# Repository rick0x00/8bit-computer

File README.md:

# 8bit-computer

This project intends to develop and distribute following the principles of the [Open Source Initiative(OSI)](https://opensource.org/osd).

The project was based on the model presented by [Wagner Rambo](https://youtube.com/playlist?list=PLZ8dBTV2_5HTB43Mhfz-TyIATkECrp8XY) and also by the project presented by [Ben Eater](https://youtube.com/playlist?list=PLowKtXNTBypGqImE405J2565dvjafglHU), both on youtube!

## Warning
I, the project maintainer ,am a beginner in this Open Source world, Git, GitHub... So I apologize in advance for any problems.

## License
At the present time this project is completely under [Apache 2.0 license](http://www.apache.org/licenses/LICENSE-2.0). All Softwares, All Electronic Designs(Schematics), All Documentation and All 3D Design.

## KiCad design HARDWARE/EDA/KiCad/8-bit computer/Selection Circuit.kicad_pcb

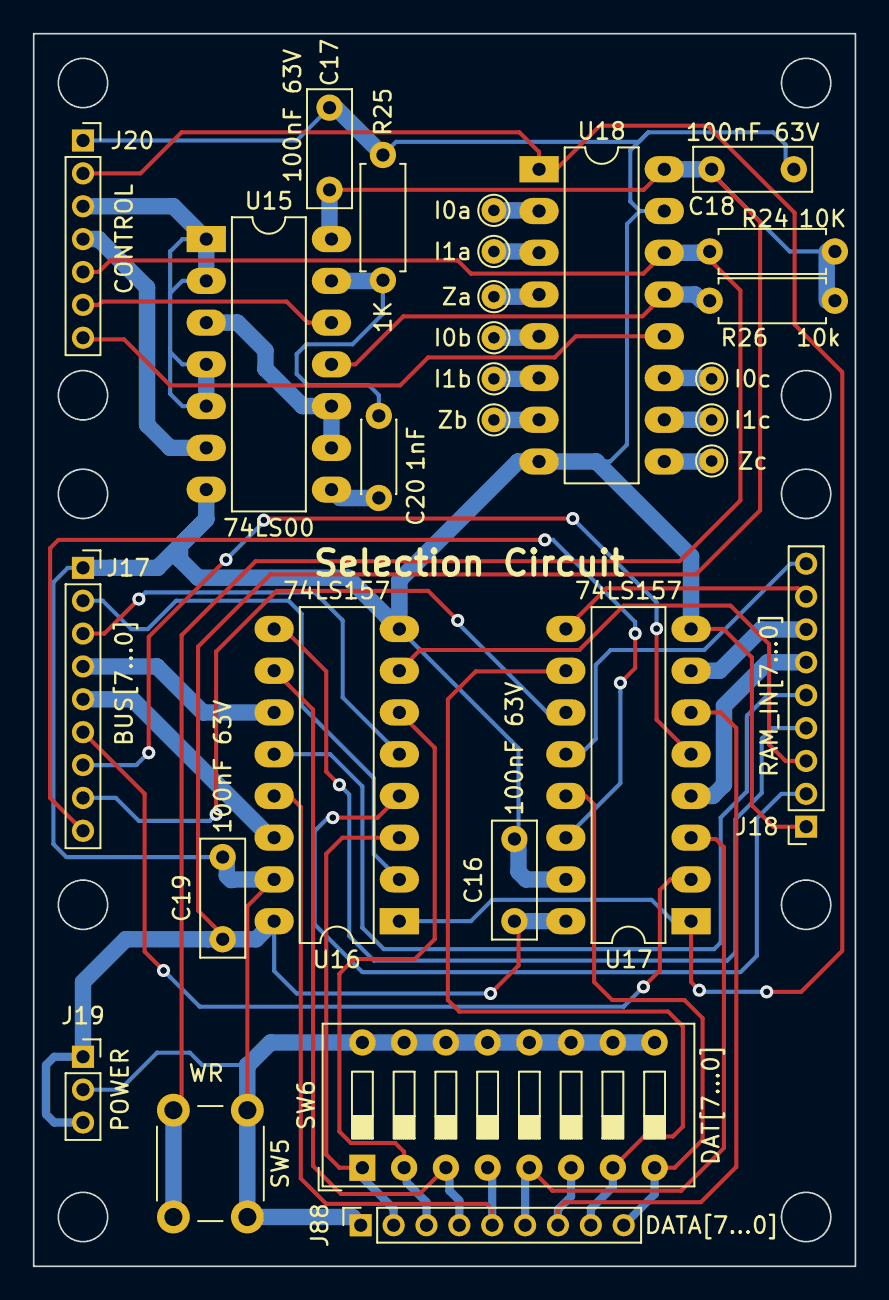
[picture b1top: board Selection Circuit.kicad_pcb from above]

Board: 2 copper layers, 50.0 x 75.0 mm, 28 parts (0 on the bottom side), 45 nets.

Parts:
C16, C17, C18, C19: 100nF 63V; C_Rect_L7.0mm_W2.5mm_P5.00mm
C20: 1nF; C_Disc_D4.3mm_W1.9mm_P5.00mm
J17: BUS[7...0]; PinSocket_1x09_P2.00mm_Vertical
J18: RAM_IN[7...0]; PinSocket_1x09_P2.00mm_Vertical
J19: POWER; PinSocket_1x03_P2.00mm_Vertical
J20: CONTROL; PinSocket_1x07_P2.00mm_Vertical
J88: DATA[7...0]; PinSocket_1x09_P2.00mm_Vertical
R24: 10K; R_Axial_DIN0207_L6.3mm_D2.5mm_P7.62mm_Horizontal
R25: 1K; R_Axial_DIN0207_L6.3mm_D2.5mm_P7.62mm_Horizontal
R26: 10k; R_Axial_DIN0207_L6.3mm_D2.5mm_P7.62mm_Horizontal
SW5: WR; SW_PUSH_6mm_H5mm
SW6: DAT[7...0]; SW_DIP_SPSTx08_Slide_9.78x22.5mm_W7.62mm_P2.54mm
TP26: I0a; TestPoint_THTPad_D1.5mm_Drill0.7mm
TP27: I1a; TestPoint_THTPad_D1.5mm_Drill0.7mm
TP28: I0b; TestPoint_THTPad_D1.5mm_Drill0.7mm
TP29: I1b; TestPoint_THTPad_D1.5mm_Drill0.7mm
TP30: I0c; TestPoint_THTPad_D1.5mm_Drill0.7mm
TP31: I1c; TestPoint_THTPad_D1.5mm_Drill0.7mm
TP32: Za; TestPoint_THTPad_D1.5mm_Drill0.7mm
TP33: Zb; TestPoint_THTPad_D1.5mm_Drill0.7mm
TP34: Zc; TestPoint_THTPad_D1.5mm_Drill0.7mm
U15: 74LS00; DIP-14_W7.62mm_LongPads
U16, U17, U18: 74LS157; DIP-16_W7.62mm_LongPads

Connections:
+5V: C16.1, C17.1, C18.1, C19.1, J19.1, J19.3, R24.1, R26.1, U15.14, U16.16, U17.16, U18.16
/dat0: J88.2, SW6.1, U16.3
/dat1: J88.3, SW6.2, U16.6
/dat2: J88.4, SW6.3, U16.10
/dat3: J88.5, SW6.4, U16.13
/dat4: J88.6, SW6.5, U17.3
/dat5: J88.7, SW6.6, U17.6
/dat6: J88.8, SW6.7, U17.10
/dat7: J88.9, SW6.8, U17.13
CLOCK: J20.3, U15.1, U15.2, U15.4, U15.5
GND: C16.2, C17.2, C18.2, C19.2, J17.1, J18.1, J19.2, J20.1, J88.1, R25.2, SW5.1, SW6.9, SW6.10, SW6.11, SW6.12, SW6.13, SW6.14, SW6.15, SW6.16, U15.7, U16.8, U16.15, U17.8, U17.15, U18.8, U18.15
unnamed: C20.1, R25.1, U15.13
unnamed: C20.2, U15.8
unnamed: R26.2, U15.11, U18.13
unnamed: TP26.1, U18.2
unnamed: TP27.1, U18.3
unnamed: TP28.1, U18.5
unnamed: TP29.1, U18.6
unnamed: TP30.1, U18.11
unnamed: TP31.1, U18.10
unnamed: TP32.1, U18.4
unnamed: TP33.1, U18.7
unnamed: TP34.1, U18.9
unnamed: U15.3, U15.9, U15.10
RAM_IN: J20.6, U15.12
WR_BUTTON: J20.5, R24.2, SW5.2, U18.14
\CLOCK: J20.4, U15.6
\Program,Run: J20.2, U16.1, U17.1, U18.1
\WE: J20.7, U18.12
bus0: J17.2, U16.2
bus1: J17.3, U16.5
bus2: J17.4, U16.11
bus3: J17.5, U16.14
bus4: J17.6, U17.2
bus5: J17.7, U17.5
bus6: J17.8, U17.11
bus7: J17.9, U17.14
ram_in0: J18.2, U16.4
ram_in1: J18.3, U16.7
ram_in2: J18.4, U16.9
ram_in3: J18.5, U16.12
ram_in4: J18.6, U17.4
ram_in5: J18.7, U17.7
ram_in6: J18.8, U17.9
ram_in7: J18.9, U17.12

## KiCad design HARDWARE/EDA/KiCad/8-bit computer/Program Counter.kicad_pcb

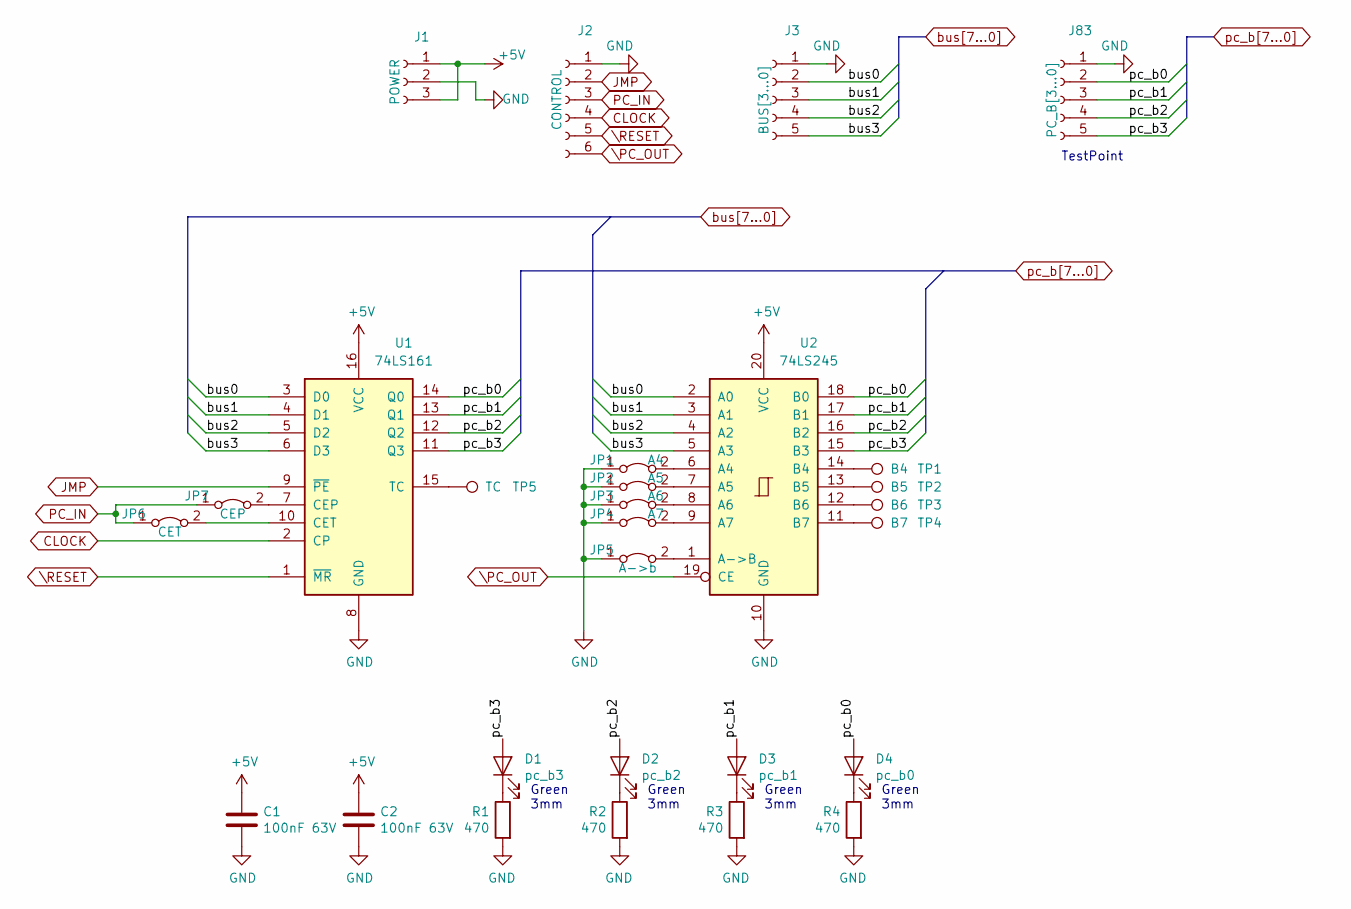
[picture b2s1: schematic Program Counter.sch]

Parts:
C1, C2: 100nF 63V; C_Rect_L7.0mm_W2.5mm_P5.00mm
D1: pc_b3; LED_D3.0mm
D2: pc_b2; LED_D3.0mm
D3: pc_b1; LED_D3.0mm
D4: pc_b0; LED_D3.0mm
J1: POWER; PinSocket_1x03_P2.00mm_Vertical
J2: CONTROL; PinSocket_1x06_P2.00mm_Vertical
J3: BUS[3...0]; PinSocket_1x05_P2.00mm_Vertical
J83: PC_B[3...0]; PinSocket_1x05_P2.00mm_Vertical
JP1: A4; TestPoint_2Pads_Pitch2.54mm_Drill0.8mm
JP2: A5; TestPoint_2Pads_Pitch2.54mm_Drill0.8mm
JP3: A6; TestPoint_2Pads_Pitch2.54mm_Drill0.8mm
JP4: A7; TestPoint_2Pads_Pitch2.54mm_Drill0.8mm
JP5: A->b; TestPoint_2Pads_Pitch2.54mm_Drill0.8mm
JP6: CET; TestPoint_2Pads_Pitch2.54mm_Drill0.8mm
JP7: CEP; TestPoint_2Pads_Pitch2.54mm_Drill0.8mm
R1, R2, R3, R4: 470; R_Axial_DIN0207_L6.3mm_D2.5mm_P7.62mm_Horizontal
TP1: B4; TestPoint_THTPad_D1.5mm_Drill0.7mm
TP2: B5; TestPoint_THTPad_D1.5mm_Drill0.7mm
TP3: B6; TestPoint_THTPad_D1.5mm_Drill0.7mm
TP4: B7; TestPoint_THTPad_D1.5mm_Drill0.7mm
TP5: TC; TestPoint_THTPad_D1.5mm_Drill0.7mm
U1: 74LS161; DIP-16_W7.62mm_LongPads
U2: 74LS245; DIP-20_W7.62mm_LongPads

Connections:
+5V: C1.1, C2.1, J1.1, J1.3, U1.16 (VCC), U2.20 (VCC)
CLOCK: J2.4, U1.2 (CP)
GND: C1.2, C2.2, J1.2, J2.1, J3.1, J83.1, JP1.1 (A), JP2.1 (A), JP3.1 (A), JP4.1 (A), JP5.1 (A), R1.2, R2.2, R3.2, R4.2, U1.8 (GND), U2.10 (GND)
JMP: J2.2, U1.9 (~PE)
unnamed: D1.1 (K), R1.1
unnamed: D2.1 (K), R2.1
unnamed: D3.1 (K), R3.1
unnamed: D4.1 (K), R4.1
unnamed: JP1.2 (B), U2.6 (A4)
unnamed: JP2.2 (B), U2.7 (A5)
unnamed: JP3.2 (B), U2.8 (A6)
unnamed: JP4.2 (B), U2.9 (A7)
unnamed: JP5.2 (B), U2.1 (A->B)
unnamed: JP6.2 (B), U1.10 (CET)
unnamed: JP7.2 (B), U1.7 (CEP)
unnamed: TP1.1, U2.14 (B4)
unnamed: TP2.1, U2.13 (B5)
unnamed: TP3.1, U2.12 (B6)
unnamed: TP4.1, U2.11 (B7)
unnamed: TP5.1, U1.15 (TC)
PC_IN: J2.3, JP6.1 (A), JP7.1 (A)
\PC_OUT: J2.6, U2.19 (CE)
\RESET: J2.5, U1.1 (~MR)
bus0: J3.2, U1.3 (D0), U2.2 (A0)
bus1: J3.3, U1.4 (D1), U2.3 (A1)
bus2: J3.4, U1.5 (D2), U2.4 (A2)
bus3: J3.5, U1.6 (D3), U2.5 (A3)
pc_b0: D4.2 (A), J83.2, U1.14 (Q0), U2.18 (B0)
pc_b1: D3.2 (A), J83.3, U1.13 (Q1), U2.17 (B1)
pc_b2: D2.2 (A), J83.4, U1.12 (Q2), U2.16 (B2)
pc_b3: D1.2 (A), J83.5, U1.11 (Q3), U2.15 (B3)

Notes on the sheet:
Green 3mm
TestPoint

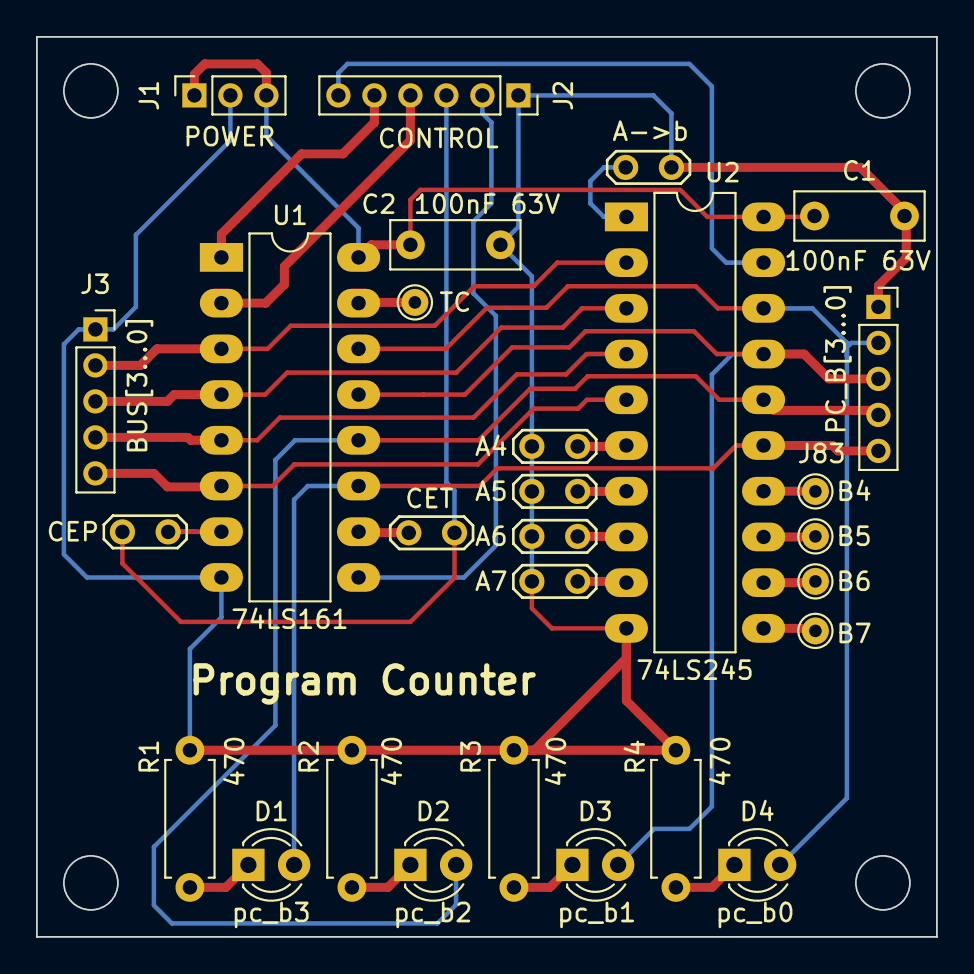
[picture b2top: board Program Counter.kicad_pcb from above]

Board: 2 copper layers, 50.0 x 50.0 mm, 28 parts (0 on the bottom side), 31 nets.

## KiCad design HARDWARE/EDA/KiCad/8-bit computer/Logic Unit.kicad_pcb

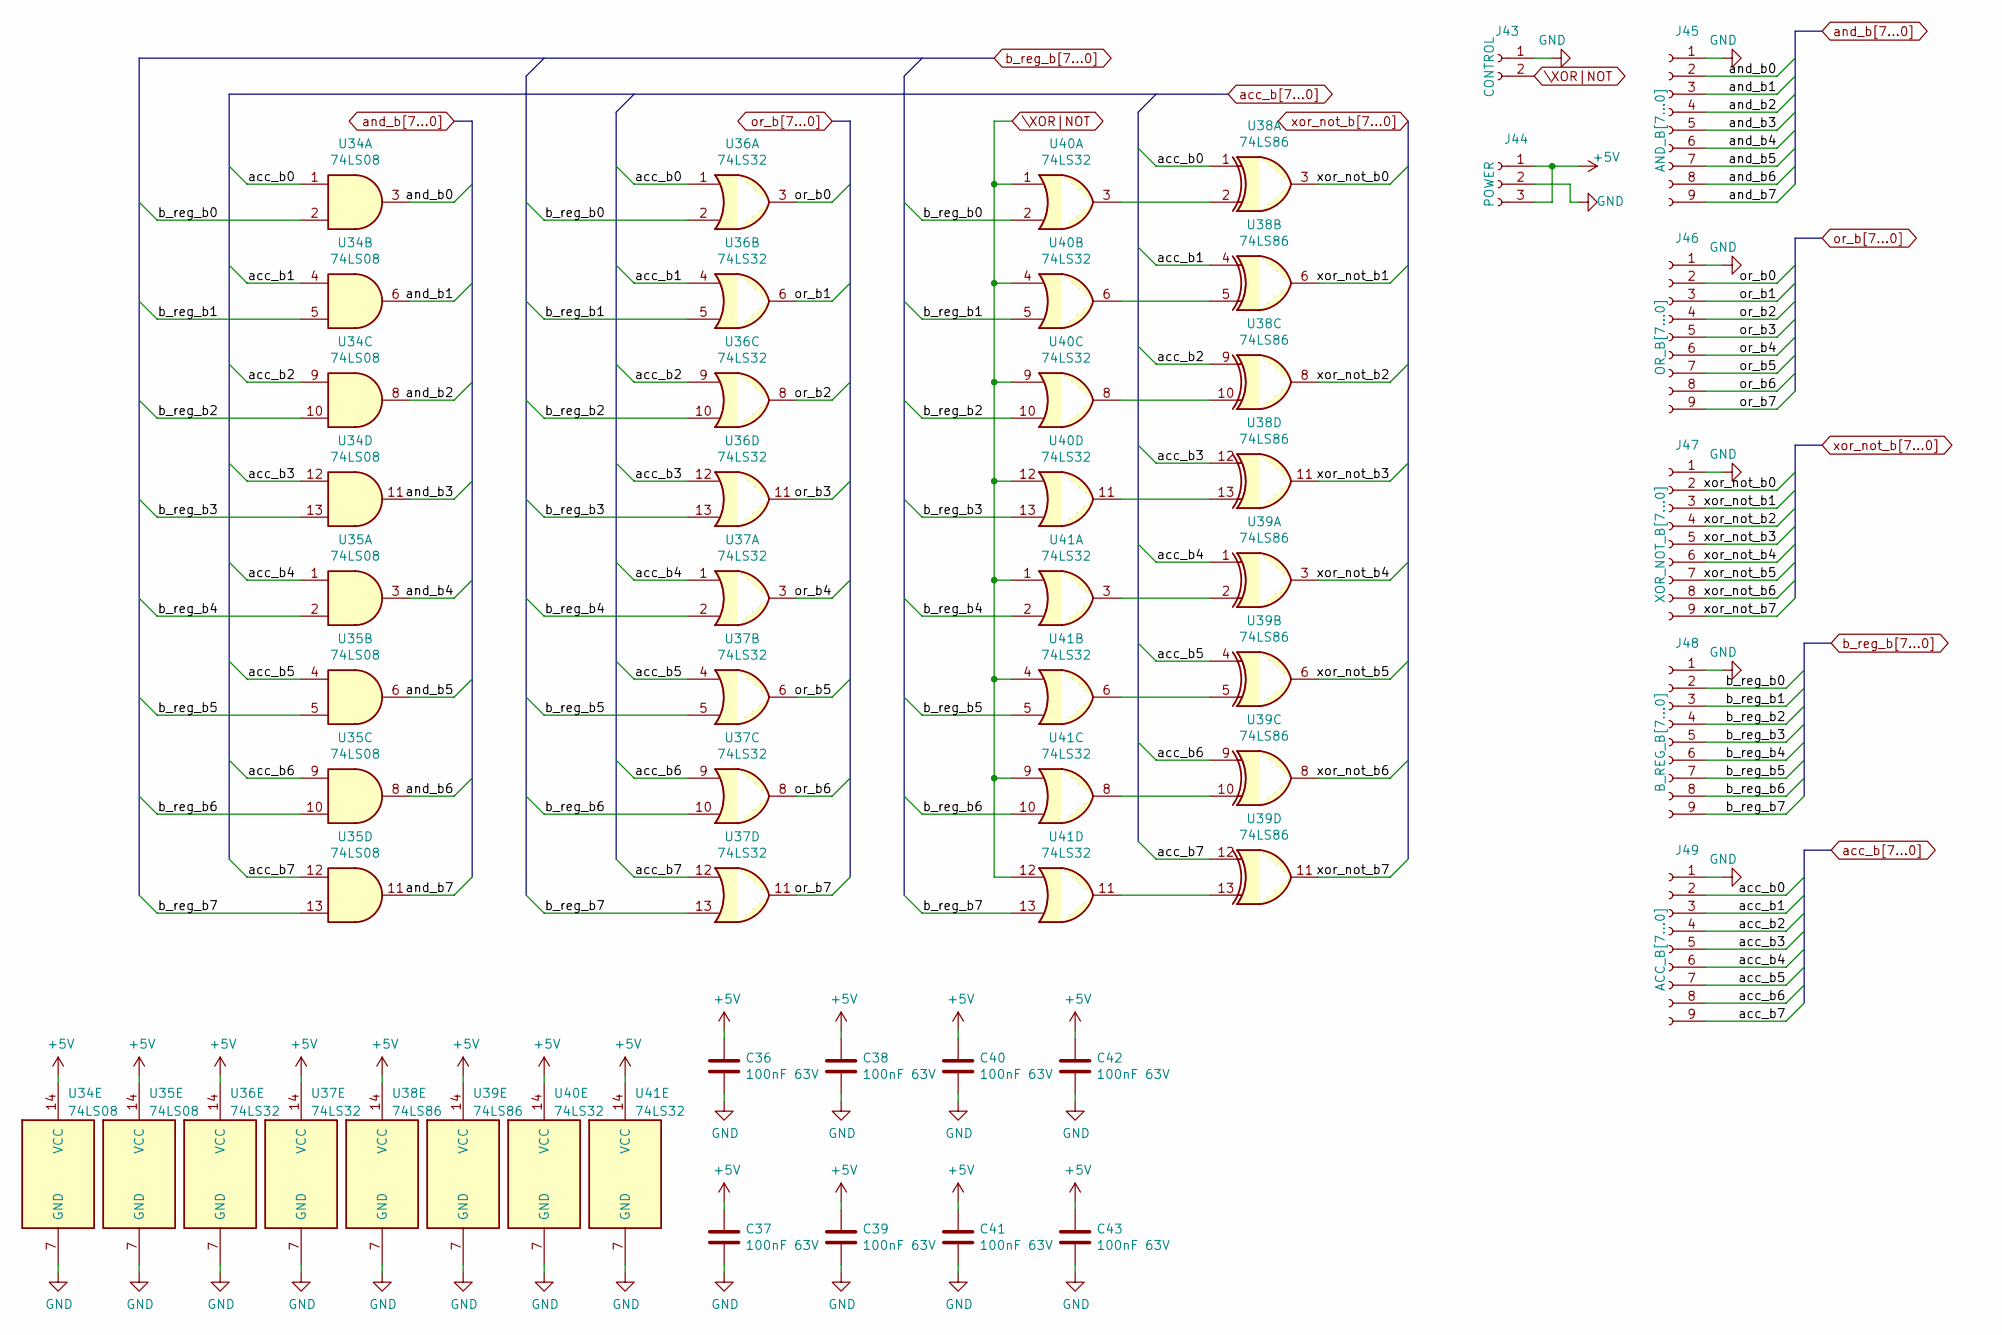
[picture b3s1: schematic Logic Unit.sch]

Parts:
C36, C37, C38, C39, C40, C41, C42, C43: 100nF 63V; C_Rect_L7.0mm_W2.5mm_P5.00mm
J43: CONTROL; PinSocket_1x02_P2.00mm_Vertical
J44: POWER; PinSocket_1x03_P2.00mm_Vertical
J45: AND_B[7...0]; PinSocket_1x09_P2.00mm_Vertical
J46: OR_B[7...0]; PinSocket_1x09_P2.00mm_Vertical
J47: XOR_NOT_B[7...0]; PinSocket_1x09_P2.00mm_Vertical
J48: B_REG_B[7...0]; PinSocket_1x09_P2.00mm_Vertical
J49: ACC_B[7...0]; PinSocket_1x09_P2.00mm_Vertical
U34, U35: 74LS08; DIP-14_W7.62mm_LongPads
U36, U37, U40, U41: 74LS32; DIP-14_W7.62mm_LongPads
U38, U39: 74LS86; DIP-14_W7.62mm_LongPads

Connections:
+5V: C36.1, C37.1, C38.1, C39.1, C40.1, C41.1, C42.1, C43.1, J44.1, J44.3, U34.14 (VCC), U35.14 (VCC), U36.14 (VCC), U37.14 (VCC), U38.14 (VCC), U39.14 (VCC), U40.14 (VCC), U41.14 (VCC)
GND: C36.2, C37.2, C38.2, C39.2, C40.2, C41.2, C42.2, C43.2, J43.1, J44.2, J45.1, J46.1, J47.1, J48.1, J49.1, U34.7 (GND), U35.7 (GND), U36.7 (GND), U37.7 (GND), U38.7 (GND), U39.7 (GND), U40.7 (GND), U41.7 (GND)
unnamed: U38.2, U40.3
unnamed: U38.5, U40.6
unnamed: U38.10, U40.8
unnamed: U38.13, U40.11
unnamed: U39.2, U41.3
unnamed: U39.5, U41.6
unnamed: U39.10, U41.8
unnamed: U39.13, U41.11
\XOR|NOT: J43.2, U40.1, U40.4, U40.9, U40.12, U41.1, U41.4, U41.9, U41.12
acc_b0: J49.2, U34.1, U36.1, U38.1
acc_b1: J49.3, U34.4, U36.4, U38.4
acc_b2: J49.4, U34.9, U36.9, U38.9
acc_b3: J49.5, U34.12, U36.12, U38.12
acc_b4: J49.6, U35.1, U37.1, U39.1
acc_b5: J49.7, U35.4, U37.4, U39.4
acc_b6: J49.8, U35.9, U37.9, U39.9
acc_b7: J49.9, U35.12, U37.12, U39.12
and_b0: J45.2, U34.3
and_b1: J45.3, U34.6
and_b2: J45.4, U34.8
and_b3: J45.5, U34.11
and_b4: J45.6, U35.3
and_b5: J45.7, U35.6
and_b6: J45.8, U35.8
and_b7: J45.9, U35.11
b_reg_b0: J48.2, U34.2, U36.2, U40.2
b_reg_b1: J48.3, U34.5, U36.5, U40.5
b_reg_b2: J48.4, U34.10, U36.10, U40.10
b_reg_b3: J48.5, U34.13, U36.13, U40.13
b_reg_b4: J48.6, U35.2, U37.2, U41.2
b_reg_b5: J48.7, U35.5, U37.5, U41.5
b_reg_b6: J48.8, U35.10, U37.10, U41.10
b_reg_b7: J48.9, U35.13, U37.13, U41.13
or_b0: J46.2, U36.3
or_b1: J46.3, U36.6
or_b2: J46.4, U36.8
or_b3: J46.5, U36.11
or_b4: J46.6, U37.3
or_b5: J46.7, U37.6
or_b6: J46.8, U37.8
or_b7: J46.9, U37.11
xor_not_b0: J47.2, U38.3
xor_not_b1: J47.3, U38.6
xor_not_b2: J47.4, U38.8
xor_not_b3: J47.5, U38.11
xor_not_b4: J47.6, U39.3
xor_not_b5: J47.7, U39.6
xor_not_b6: J47.8, U39.8
xor_not_b7: J47.9, U39.11

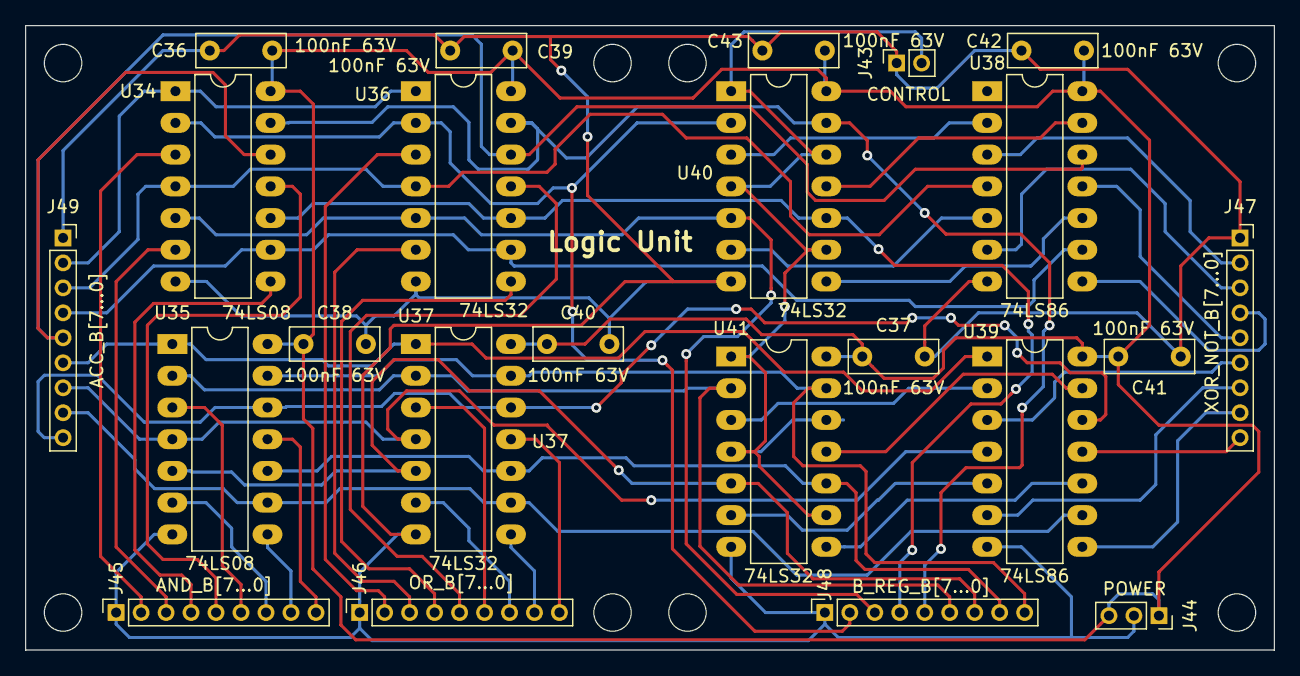
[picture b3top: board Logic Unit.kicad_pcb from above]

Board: 2 copper layers, 100.0 x 50.0 mm, 23 parts (0 on the bottom side), 51 nets.

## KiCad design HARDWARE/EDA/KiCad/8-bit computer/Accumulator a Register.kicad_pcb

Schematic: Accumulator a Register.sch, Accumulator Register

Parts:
C24, C25, C26: 100nF 63V; C_Rect_L7.0mm_W2.5mm_P5.00mm
D27: acc_b7; LED_D3.0mm
D28: acc_b6; LED_D3.0mm
D29: acc_b5; LED_D3.0mm
D30: acc_b4; LED_D3.0mm
D31: acc_b3; LED_D3.0mm
D32: acc_b2; LED_D3.0mm
D33: acc_b1; LED_D3.0mm
D34: acc_b0; LED_D3.0mm
J25: POWER; PinSocket_1x03_P2.00mm_Vertical
J26: CONTROL; PinSocket_1x05_P2.00mm_Vertical
J27: ACC_B[7...0]; PinSocket_1x09_P2.00mm_Vertical
J28: BUS[7...0]; PinSocket_1x09_P2.00mm_Vertical
JP25, JP29: Oe2; TestPoint_2Pads_Pitch2.54mm_Drill0.8mm
JP26, JP30: E2; TestPoint_2Pads_Pitch2.54mm_Drill0.8mm
JP27, JP31: Oe1; TestPoint_2Pads_Pitch2.54mm_Drill0.8mm
JP28, JP32: E1; TestPoint_2Pads_Pitch2.54mm_Drill0.8mm
JP33: A->B; TestPoint_2Pads_Pitch2.54mm_Drill0.8mm
R35, R36, R37, R38, R39, R40, R41, R42: 470; R_Axial_DIN0207_L6.3mm_D2.5mm_P7.62mm_Horizontal
U22, U23: 74LS173; DIP-16_W7.62mm_LongPads
U24: 74LS245; DIP-20_W7.62mm_LongPads

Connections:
+5V: C24.1, C25.1, C26.1, J25.1, J25.3, JP33.1 (A), U22.16, U23.16, U24.20 (VCC)
CLOCK: J26.2, U22.7, U23.7
GND: C24.2, C25.2, C26.2, J25.2, J26.1, J27.1, J28.1, JP25.1 (A), JP27.1 (A), JP29.1 (A), JP31.1 (A), R35.2, R36.2, R37.2, R38.2, R39.2, R40.2, R41.2, R42.2, U22.8, U23.8, U24.10 (GND)
unnamed: D27.1 (K), R35.1
unnamed: D28.1 (K), R36.1
unnamed: D29.1 (K), R37.1
unnamed: D30.1 (K), R38.1
unnamed: D31.1 (K), R39.1
unnamed: D32.1 (K), R40.1
unnamed: D33.1 (K), R41.1
unnamed: D34.1 (K), R42.1
unnamed: JP25.2 (B), U22.2
unnamed: JP26.2 (B), U22.10
unnamed: JP27.2 (B), U22.1
unnamed: JP28.2 (B), U22.9
unnamed: JP29.2 (B), U23.2
unnamed: JP30.2 (B), U23.10
unnamed: JP31.2 (B), U23.1
unnamed: JP32.2 (B), U23.9
unnamed: JP33.2 (B), U24.1 (A->B)
RESET: J26.3, U22.15, U23.15
\ACC_IN: J26.4, JP26.1 (A), JP28.1 (A), JP30.1 (A), JP32.1 (A)
\ACC_OUT: J26.5, U24.19 (CE)
acc_b0: D34.2 (A), J27.2, U22.3, U24.2 (A0)
acc_b1: D33.2 (A), J27.3, U22.4, U24.3 (A1)
acc_b2: D32.2 (A), J27.4, U22.5, U24.4 (A2)
acc_b3: D31.2 (A), J27.5, U22.6, U24.5 (A3)
acc_b4: D30.2 (A), J27.6, U23.3, U24.6 (A4)
acc_b5: D29.2 (A), J27.7, U23.4, U24.7 (A5)
acc_b6: D28.2 (A), J27.8, U23.5, U24.8 (A6)
acc_b7: D27.2 (A), J27.9, U23.6, U24.9 (A7)
bus0: J28.2, U22.14, U24.18 (B0)
bus1: J28.3, U22.13, U24.17 (B1)
bus2: J28.4, U22.12, U24.16 (B2)
bus3: J28.5, U22.11, U24.15 (B3)
bus4: J28.6, U23.14, U24.14 (B4)
bus5: J28.7, U23.13, U24.13 (B5)
bus6: J28.8, U23.12, U24.12 (B6)
bus7: J28.9, U23.11, U24.11 (B7)

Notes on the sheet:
Green 3mm
Red 3mm

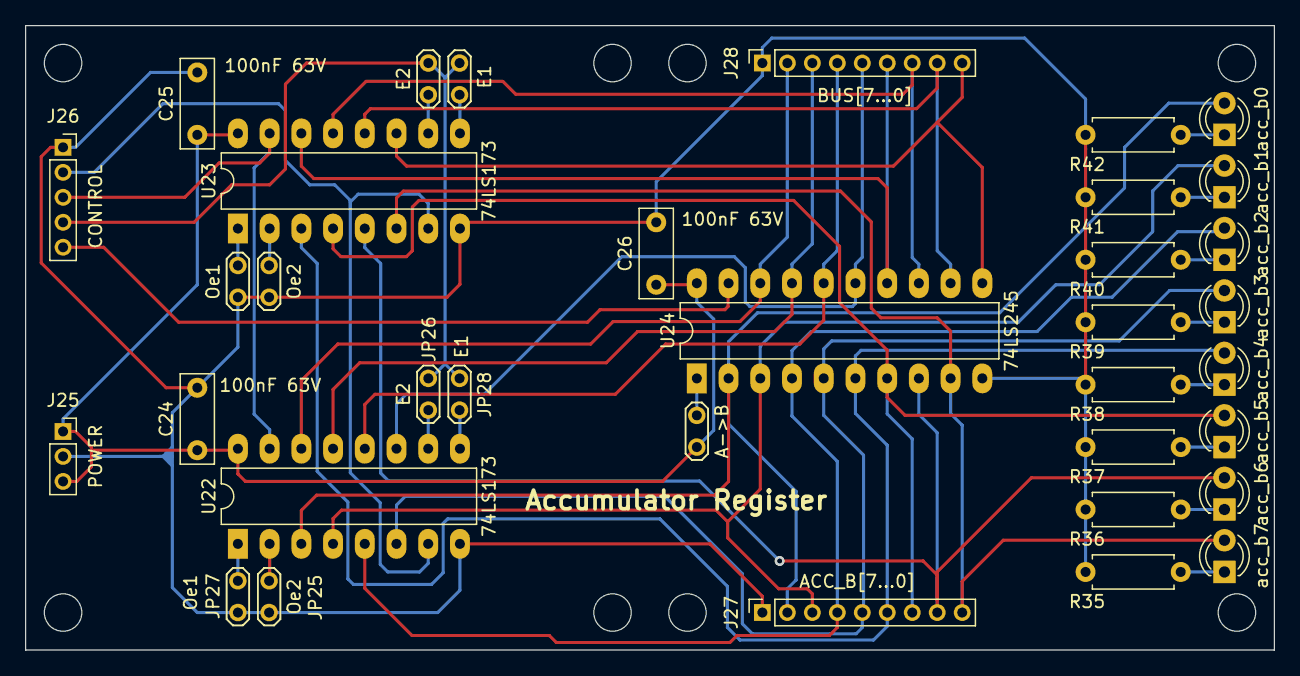
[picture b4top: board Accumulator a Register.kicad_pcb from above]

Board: 2 copper layers, 100.0 x 50.0 mm, 35 parts (0 on the bottom side), 39 nets.

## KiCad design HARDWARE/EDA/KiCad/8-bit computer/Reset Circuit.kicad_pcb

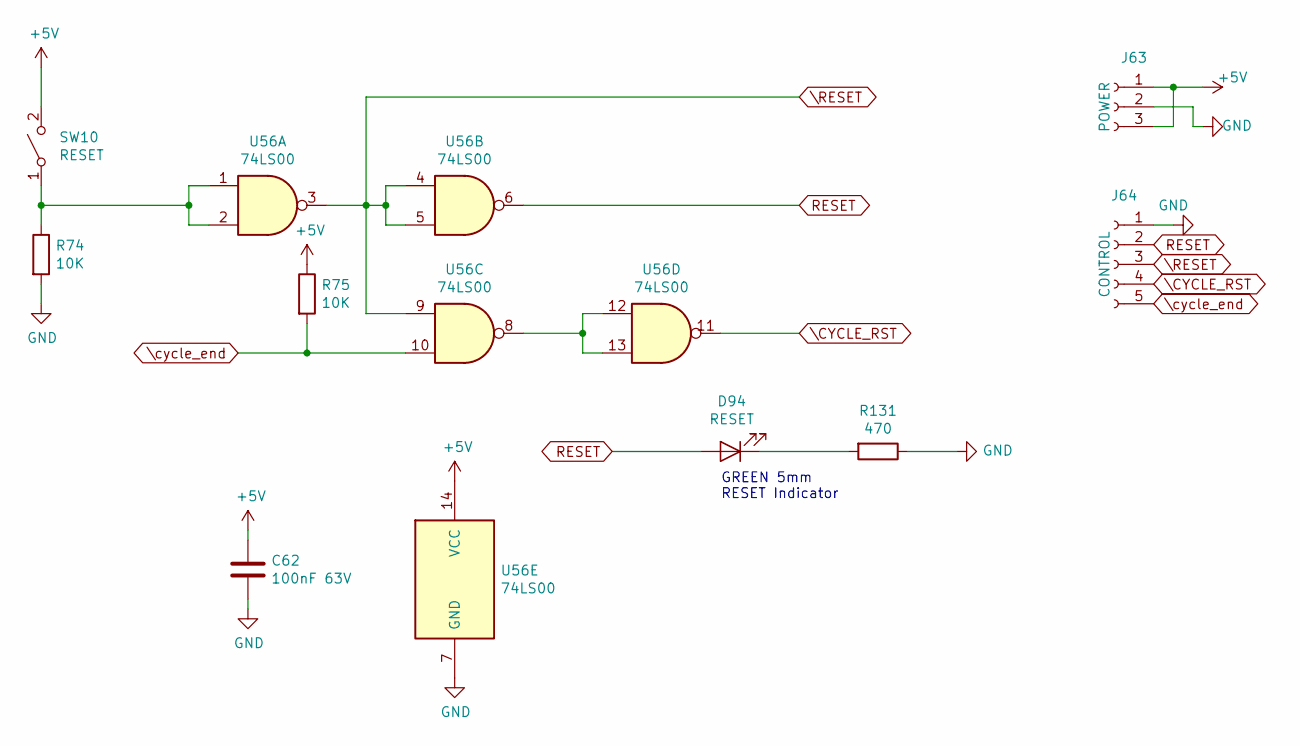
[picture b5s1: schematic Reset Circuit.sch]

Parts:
C62: 100nF 63V; C_Rect_L7.0mm_W2.5mm_P5.00mm
D94: RESET; LED_D3.0mm
J63: POWER; PinSocket_1x03_P2.00mm_Vertical
J64: CONTROL; PinSocket_1x05_P2.00mm_Vertical
R74, R75: 10K; R_Axial_DIN0207_L6.3mm_D2.5mm_P7.62mm_Horizontal
R131: 470; R_Axial_DIN0207_L6.3mm_D2.5mm_P7.62mm_Horizontal
SW10: RESET; SW_PUSH_6mm_H5mm
U56: 74LS00; DIP-14_W7.62mm_LongPads

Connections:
+5V: C62.1, J63.1, J63.3, R75.1, SW10.2 (B), U56.14 (VCC)
GND: C62.2, J63.2, J64.1, R74.2, R131.1, U56.7 (GND)
unnamed: D94.1 (K), R131.2
unnamed: R74.1, SW10.1 (A), U56.1, U56.2
unnamed: U56.8, U56.12, U56.13
RESET: D94.2 (A), J64.2, U56.6
\CYCLE_RST: J64.4, U56.11
\RESET: J64.3, U56.3, U56.4, U56.5, U56.9
\cycle_end: J64.5, R75.2, U56.10

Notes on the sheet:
GREEN 5mm RESET Indicator

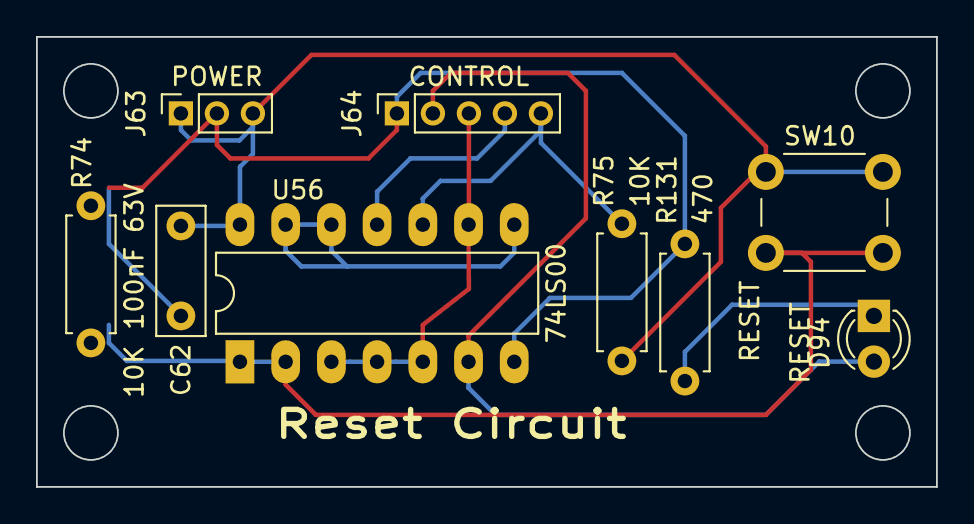
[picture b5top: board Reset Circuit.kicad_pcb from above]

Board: 2 copper layers, 50.0 x 25.0 mm, 9 parts (0 on the bottom side), 9 nets.

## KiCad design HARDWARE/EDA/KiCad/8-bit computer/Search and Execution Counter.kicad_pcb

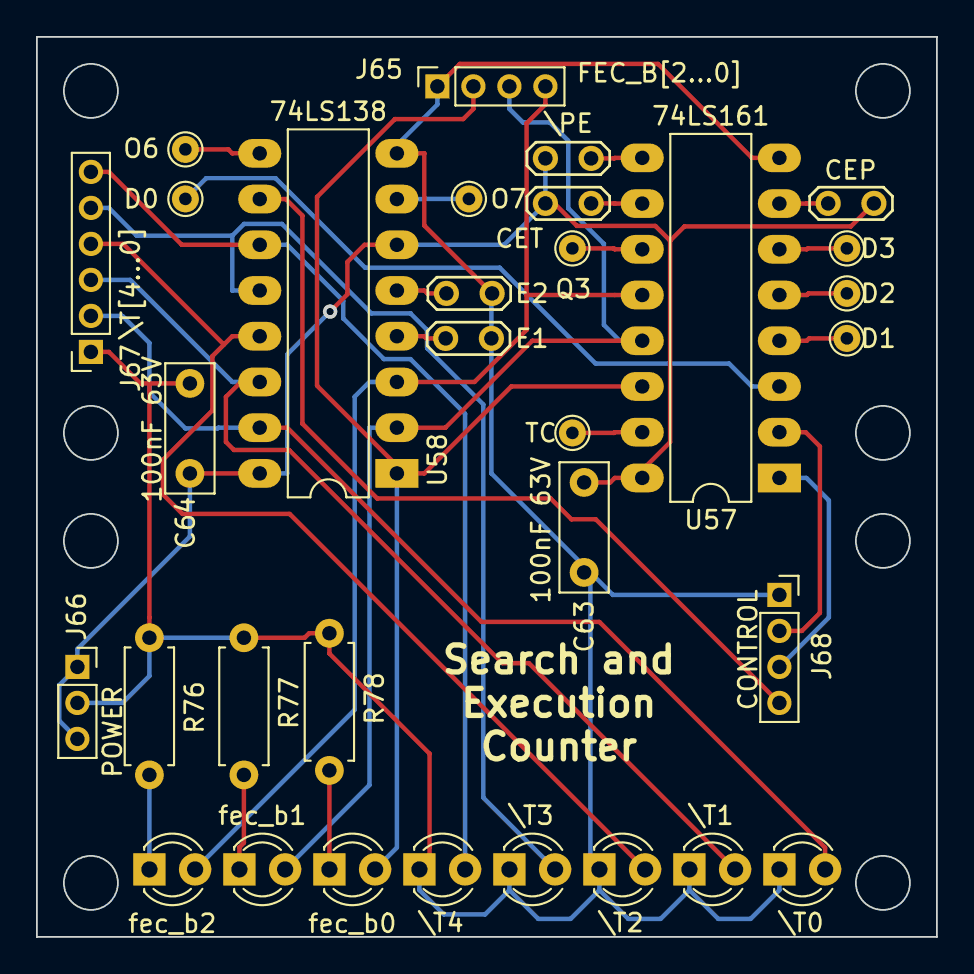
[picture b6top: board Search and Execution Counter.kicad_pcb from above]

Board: 2 copper layers, 50.0 x 50.0 mm, 32 parts (0 on the bottom side), 29 nets.

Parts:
C63, C64: 100nF 63V; C_Rect_L7.0mm_W2.5mm_P5.00mm
D60: fec_b2; LED_D3.0mm_Clear
D61: fec_b1; LED_D3.0mm_Clear
D62: fec_b0; LED_D3.0mm_Clear
D63: \T4; LED_D3.0mm_Clear
D64: \T3; LED_D3.0mm_Clear
D65: \T2; LED_D3.0mm_Clear
D66: \T1; LED_D3.0mm_Clear
D67: \T0; LED_D3.0mm_Clear
J65: FEC_B[2...0]; PinSocket_1x04_P2.00mm_Vertical
J66: POWER; PinSocket_1x03_P2.00mm_Vertical
J67: \T[4...0]; PinSocket_1x06_P2.00mm_Vertical
J68: CONTROL; PinSocket_1x04_P2.00mm_Vertical
JP75: CEP; TestPoint_2Pads_Pitch2.54mm_Drill0.8mm
JP76: \PE; TestPoint_2Pads_Pitch2.54mm_Drill0.8mm
JP77: CET; TestPoint_2Pads_Pitch2.54mm_Drill0.8mm
JP78: E2; TestPoint_2Pads_Pitch2.54mm_Drill0.8mm
JP79: E1; TestPoint_2Pads_Pitch2.54mm_Drill0.8mm
R76, R77, R78: 330; R_Axial_DIN0207_L6.3mm_D2.5mm_P7.62mm_Horizontal
TP46: D0; TestPoint_THTPad_D1.5mm_Drill0.7mm
TP47: D1; TestPoint_THTPad_D1.5mm_Drill0.7mm
TP48: D2; TestPoint_THTPad_D1.5mm_Drill0.7mm
TP49: D3; TestPoint_THTPad_D1.5mm_Drill0.7mm
TP50: Q3; TestPoint_THTPad_D1.5mm_Drill0.7mm
TP51: TC; TestPoint_THTPad_D1.5mm_Drill0.7mm
TP52: O6; TestPoint_THTPad_D1.5mm_Drill0.7mm
TP53: O7; TestPoint_THTPad_D1.5mm_Drill0.7mm
U57: 74LS161; DIP-16_W7.62mm_LongPads
U58: 74LS138; DIP-16_W7.62mm_LongPads

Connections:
+5V: C63.1, C64.1, J66.1, J66.3, JP75.1, JP76.1, JP77.1, U57.16, U58.6, U58.16
/\T0: D67.2, J67.2, U58.15
/\T1: D66.2, J67.3, U58.14
/\T2: D65.2, J67.4, U58.13
/\T3: D64.2, J67.5, U58.12
/\T4: D63.2, J67.6, U58.11
GND: C63.2, C64.2, D63.1, D64.1, D65.1, D66.1, D67.1, J65.1, J66.2, J67.1, J68.1, JP78.1, JP79.1, R76.2, R77.2, R78.2, U57.8, U58.8
unnamed: D60.1, R76.1
unnamed: D61.1, R77.1
unnamed: D62.1, R78.1
unnamed: JP75.2, U57.7
unnamed: JP76.2, U57.9
unnamed: JP77.2, U57.10
unnamed: JP78.2, U58.5
unnamed: JP79.2, U58.4
unnamed: TP46.1, U57.3
unnamed: TP47.1, U57.4
unnamed: TP48.1, U57.5
unnamed: TP49.1, U57.6
unnamed: TP50.1, U57.11
unnamed: TP51.1, U57.15
unnamed: TP52.1, U58.9
unnamed: TP53.1, U58.7
\CLOCK: J68.2, U57.2
\CYCLE_RST: J68.3, U57.1
\cycle_end: J68.4, U58.10
fec_b0: D62.2, J65.2, U57.14, U58.1
fec_b1: D61.2, J65.3, U57.13, U58.2
fec_b2: D60.2, J65.4, U57.12, U58.3

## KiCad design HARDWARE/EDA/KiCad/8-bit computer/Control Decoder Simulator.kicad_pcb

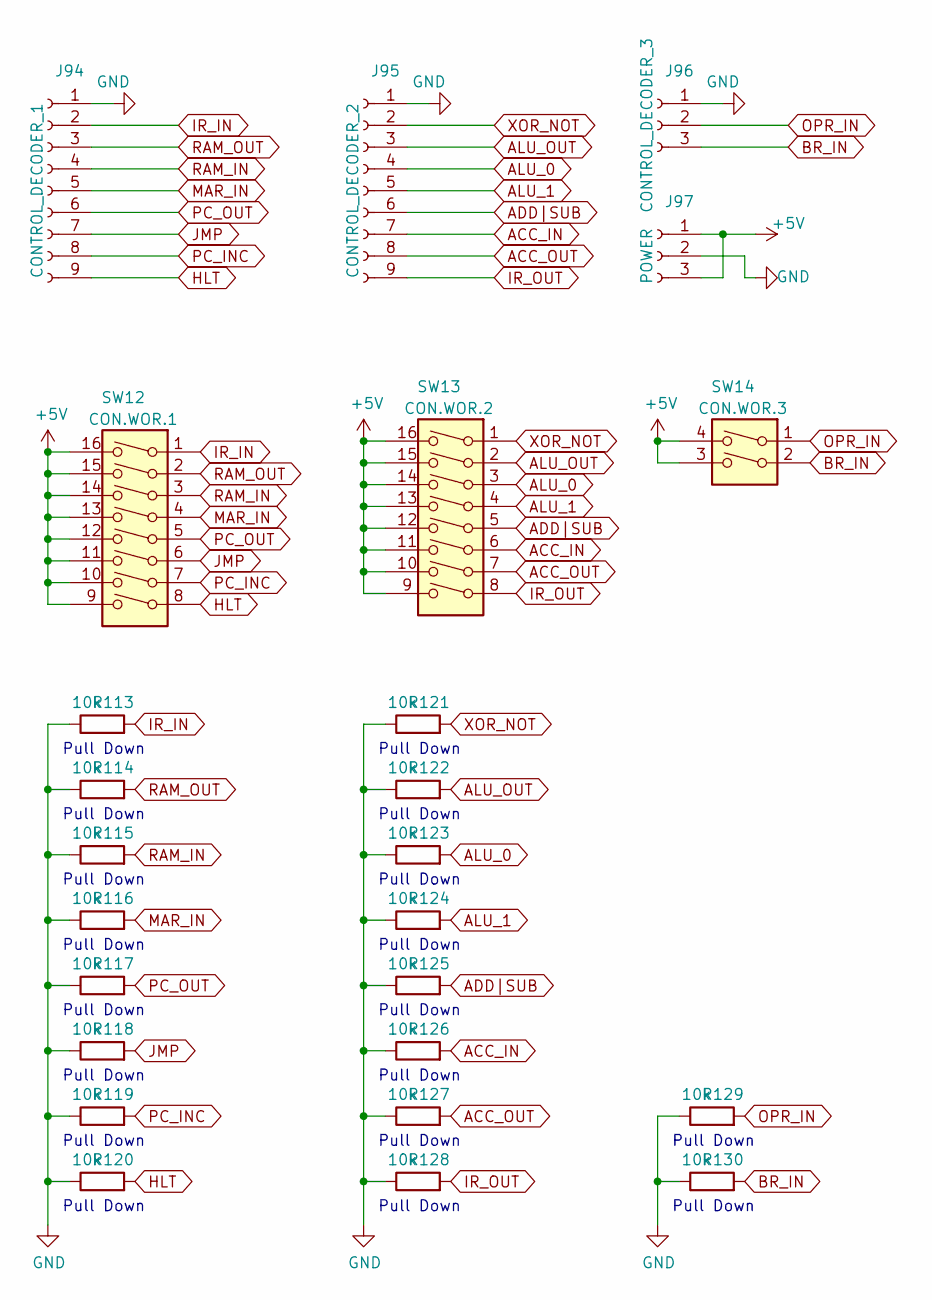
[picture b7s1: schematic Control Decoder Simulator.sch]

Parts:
J94: CONTROL_DECODER_1; PinSocket_1x09_P2.00mm_Vertical
J95: CONTROL_DECODER_2; PinSocket_1x09_P2.00mm_Vertical
J96: CONTROL_DECODER_3; PinSocket_1x03_P2.00mm_Vertical
J97: POWER; PinSocket_1x03_P2.00mm_Vertical
R113, R114, R115, R116, R117, R118, R119, R120, R121, R122, R123, R124, R125, R126, R127, R128, R129, R130: 10k; R_Axial_DIN0207_L6.3mm_D2.5mm_P7.62mm_Horizontal
SW12: CON.WOR.1; SW_DIP_SPSTx08_Slide_9.78x22.5mm_W7.62mm_P2.54mm
SW13: CON.WOR.2; SW_DIP_SPSTx08_Slide_9.78x22.5mm_W7.62mm_P2.54mm
SW14: CON.WOR.3; SW_DIP_SPSTx02_Slide_9.78x7.26mm_W7.62mm_P2.54mm

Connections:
+5V: J97.1, J97.3, SW12.9, SW12.10, SW12.11, SW12.12, SW12.13, SW12.14, SW12.15, SW12.16, SW13.9, SW13.10, SW13.11, SW13.12, SW13.13, SW13.14, SW13.15, SW13.16, SW14.3, SW14.4
ACC_IN: J95.7, R126.2, SW13.6
ACC_OUT: J95.8, R127.2, SW13.7
ADD|SUB: J95.6, R125.2, SW13.5
ALU_0: J95.4, R123.2, SW13.3
ALU_1: J95.5, R124.2, SW13.4
ALU_OUT: J95.3, R122.2, SW13.2
BR_IN: J96.3, R130.2, SW14.2
GND: J94.1, J95.1, J96.1, J97.2, R113.1, R114.1, R115.1, R116.1, R117.1, R118.1, R119.1, R120.1, R121.1, R122.1, R123.1, R124.1, R125.1, R126.1, R127.1, R128.1, R129.1, R130.1
HLT: J94.9, R120.2, SW12.8
IR_IN: J94.2, R113.2, SW12.1
IR_OUT: J95.9, R128.2, SW13.8
JMP: J94.7, R118.2, SW12.6
MAR_IN: J94.5, R116.2, SW12.4
OPR_IN: J96.2, R129.2, SW14.1
PC_INC: J94.8, R119.2, SW12.7
PC_OUT: J94.6, R117.2, SW12.5
RAM_IN: J94.4, R115.2, SW12.3
RAM_OUT: J94.3, R114.2, SW12.2
XOR_NOT: J95.2, R121.2, SW13.1

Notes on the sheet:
Pull Down

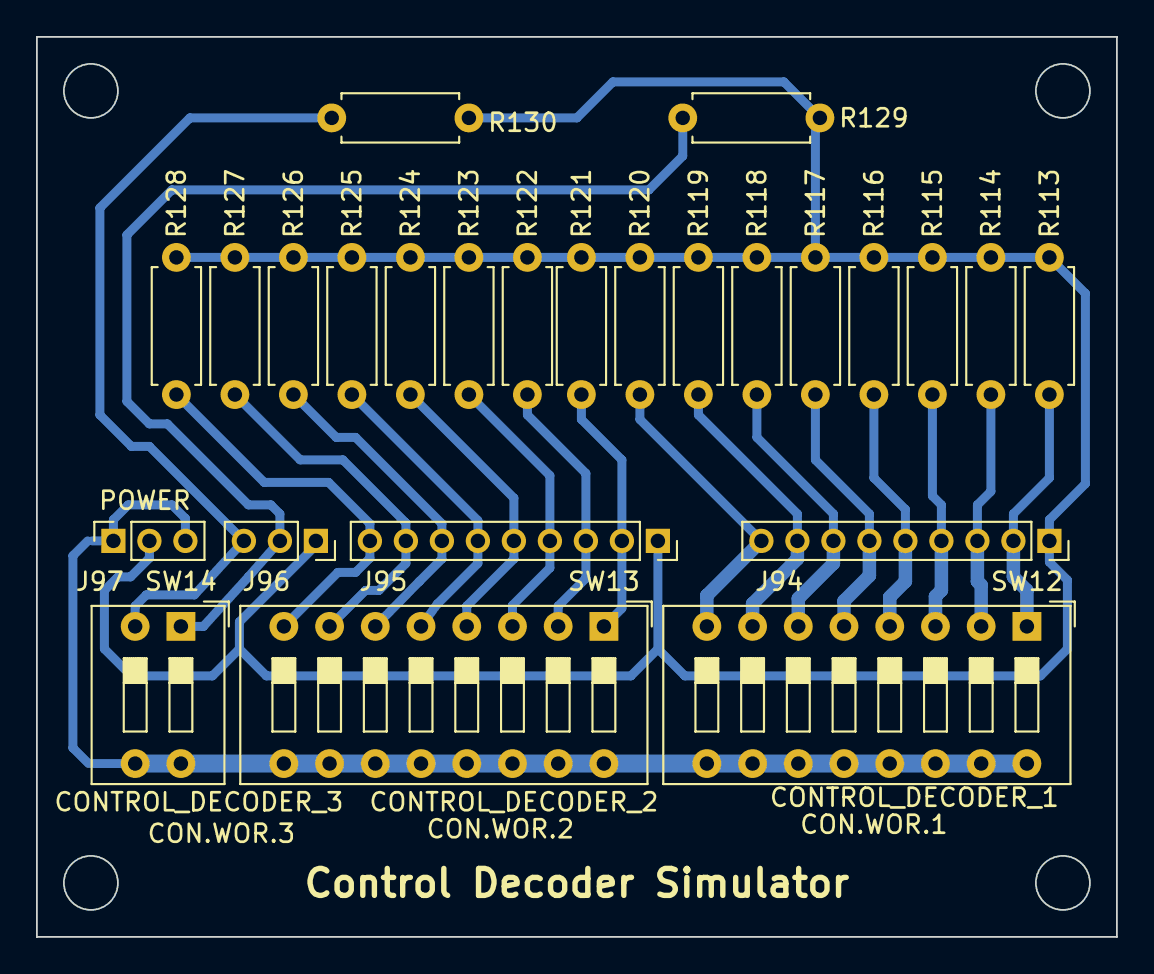
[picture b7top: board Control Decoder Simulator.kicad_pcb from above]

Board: 2 copper layers, 60.0 x 50.0 mm, 25 parts (0 on the bottom side), 20 nets.
